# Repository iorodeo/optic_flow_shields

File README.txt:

Arduino shields for use  ADNSD3080 optical flow sensors (2x). The shield also
breaks out 5V, GND, various DIO and analog inputs on a screw terminal block.
The optic flow sensors connect to the PCB via two 5x2 shrouded (keyed)
headers. 

An adaptor PCB for the ADNS3080 optic flow sensor sensor is also provided so
that the optic flow sensor can be connected to the shield via a 10-pin ribbon cable
via a 5x2 shoured header.

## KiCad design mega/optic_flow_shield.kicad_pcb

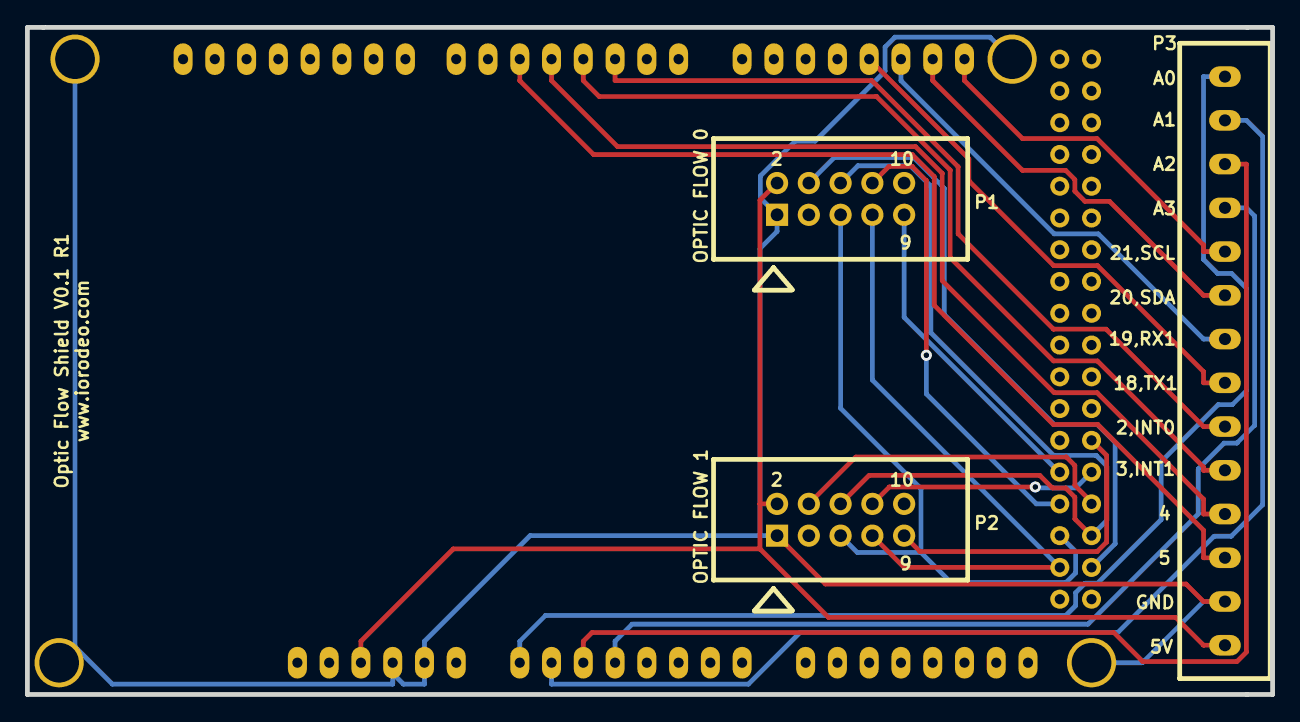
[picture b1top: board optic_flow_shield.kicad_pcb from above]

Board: 2 copper layers, 99.6 x 53.3 mm, 4 parts (0 on the bottom side), 23 nets.

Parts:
P1: OPTIC FLOW 0; 5X2_SHRD_HEADER
P2: OPTIC FLOW 1; 5X2_SHRD_HEADER
P3: CONN_14; TERMBLOCK_14
SHIELD1: ARDUINO_MEGA_SHIELD

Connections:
/5V: P1.2, P2.2, P3.1, SHIELD1.5V
/AD0: P3.14, SHIELD1.AD0
/AD1: P3.13, SHIELD1.AD1
/AD2: P3.12, SHIELD1.AD2
/AD3: P3.11, SHIELD1.AD3
/CS0: P1.4, SHIELD1.53
/CS1: P2.4, SHIELD1.49
/D2_INT0: P3.6, SHIELD1.2
/D3_INT1: P3.5, SHIELD1.3
/D4: P3.4, SHIELD1.4
/D5: P3.3, SHIELD1.5
/D18_TX1: P3.7, SHIELD1.18
/D19_RX1: P3.8, SHIELD1.19
/D20_SDA: P3.9, SHIELD1.20
/D21_SCL: P3.10, SHIELD1.21
/MISO: P1.5, P2.5, SHIELD1.50
/MOSI: P1.6, P2.6, SHIELD1.51
/NPD0: P1.9, SHIELD1.46
/NPD1: P2.9, SHIELD1.45
/RST0: P1.8, SHIELD1.48
/RST1: P2.8, SHIELD1.47
/SCK: P1.7, P2.7, SHIELD1.52
GND: P1.1, P2.1, P3.2, SHIELD1.GND1, SHIELD1.GND2

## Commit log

2015-06-24 Project creation.
2015-06-25 Added .zip archives of gerber files for ordering boards.
